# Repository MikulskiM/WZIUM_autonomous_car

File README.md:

# WZIUM_autonomous_car - ROS section
Autonomous RC car project

Clone repo and place it in 'wzium' directory. Please place this repo in user's home directory as some environmental variables depend on it later.
```
git clone https://github.com/MikulskiM/WZIUM_autonomous_car.git wzium
```

## Requirements
TODO: place link to raspberry pi image 

### ROS Melodic
Available only on Ubuntu 18.04 LTS.
Link to install [here](http://wiki.ros.org/melodic/Installation/Ubuntu).

Some setup in ~/.bashrc file:
```
# Networking - substitute <ip_address> with raspberry ip address
export ROS_MASTER_URI=http://<ip_address>:11311
export ROS_IP=<ip_address>

# Add to ros packages - can cause warning before first compile
export ROS_PACKAGE_PATH=~/wzium:${ROS_PACKAGE_PATH}
export CMAKE_PREFIX_PATH=~/wzium/devel:${CMAKE_PREFIX_PATH}

# Makes your package visible to ros at creating new console
source ~/wzium/devel/setup.bash
```

After setup you should bashrc so the changes can take place
```
source ~/.bashrc
```

To install ROS packages dependencies (run from workspace root directory):
```
rosdep install --from-paths src --ignore-src -r -y
```

## Build
Enter workspace root directory ('wzium')
```
catkin_make
source devel/setup.bash
```

Building packages can get lousy. You can add flag --pkg to catkin_make to specify packages that are to be built, e.g. ```catkin_make --pkg wzium```. This can save a lot of time.

## Usage
You can run nodes directly (you have to run ```roscore``` first in some console window), then run node e.g.:
```
# cpp nodes have to be built
rosrun wzium example_cpp_node
# python nodes have to be made executable
rosrun wzium example_python_node
```
or via launch files (no roscore needed) e.g.:
```
roslaunch wzium example_launch.launch
```

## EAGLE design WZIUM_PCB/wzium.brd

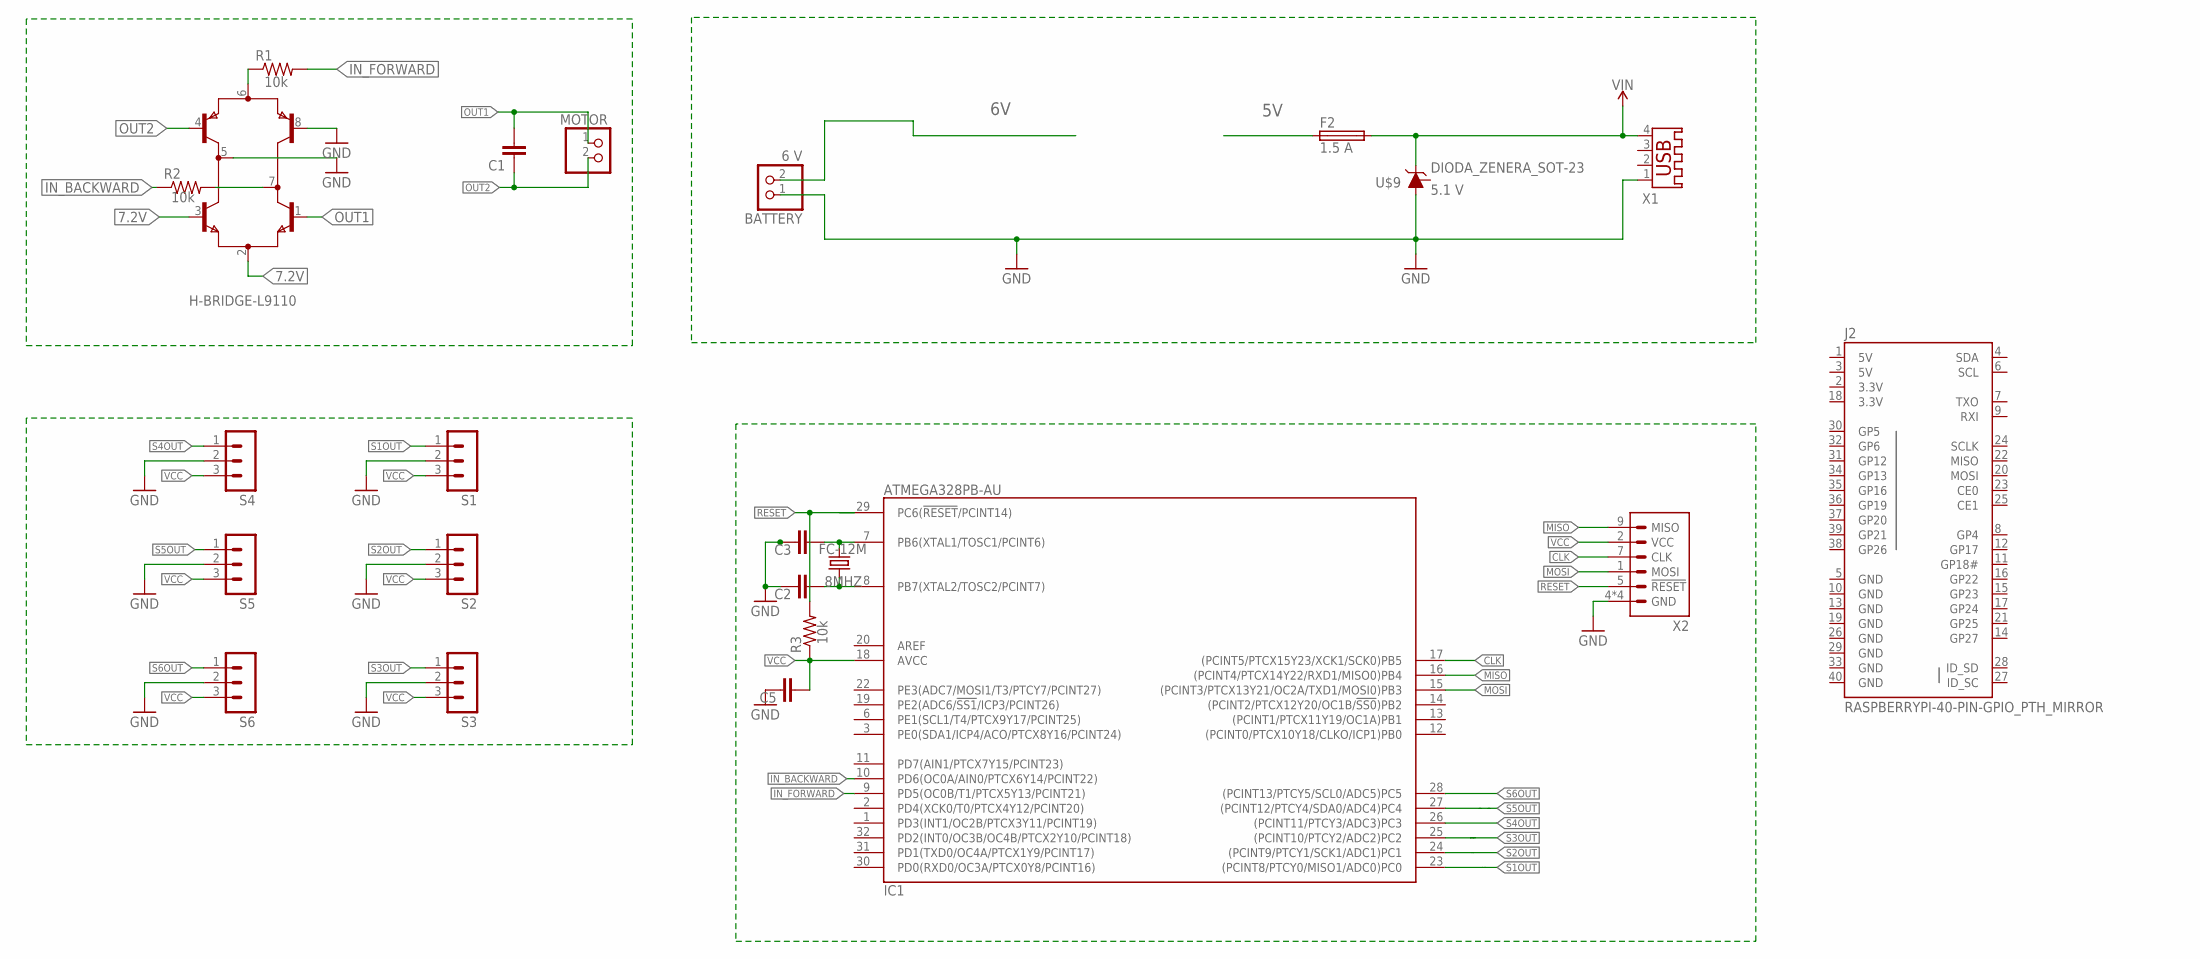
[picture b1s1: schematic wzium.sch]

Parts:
8MHZ: FC-12M
BATTERY: 6 V; 1X02
C1, C2, C3, C5: C-EUC0805; C0805
F2: 1.5 A; SH22,5
H-BRIDGE-L9110: H-BRIDGE; SM8
IC1: ATMEGA328PB-AU; QFP32_7X7_0.80
J2: RASPBERRYPI-40-PIN-GPIO_PTH_MIRROR; 2X20_SHROUDED
MOTOR: PINHD-1X2; 1X02
R1, R2, R3: 10k; R0805
S1, S2, S3, S4, S5, S6: MA03-1
U$9: DIODA_ZENERA_SOT-23; SOT23-3
X1: USB-A003
X2: MISO_MOSIIDC-10V; IDC-10V

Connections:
3.3V: J2.2 (3.3V), J2.18 (3.3V)
5V: F2.1, J2.1 (5V), J2.3 (5V)
6V: BATTERY.2
7.2V: H-BRIDGE-L9110.2 (E2E3), H-BRIDGE-L9110.3 (B2)
CLK: IC1.17 ((PCINT5/PTCX15Y23/XCK1/SCK0)PB5), X2.7 (CLK)
GND: BATTERY.1, C2.2, C3.2, C5.2, H-BRIDGE-L9110.5 (C1C2), H-BRIDGE-L9110.8 (B4), IC1.5 (GND), IC1.21 (GND), J2.5 (GND), J2.10 (GND), J2.13 (GND), J2.19 (GND), J2.26 (GND), J2.29 (GND), J2.33 (GND), J2.40 (GND), S1.2, S2.2, S3.2, S4.2, S5.2, S6.2, U$9.1 (A), X1.1, X2.4 (GND), X2.6 (GND), X2.8 (GND), X2.10 (GND)
IN_BACKWARD: IC1.10 (PD6(OC0A/AIN0/PTCX6Y14/PCINT22)), R2.1
IN_FORWARD: IC1.9 (PD5(OC0B/T1/PTCX5Y13/PCINT21)), R1.2
MISO: IC1.16 ((PCINT4/PTCX14Y22/RXD1/MISO0)PB4), X2.9 (MISO)
MOSI: IC1.15 ((PCINT3/PTCX13Y21/OC2A/TXD1/MOSI0)PB3), X2.1 (MOSI)
unnamed: H-BRIDGE-L9110.7 (C3C4), R2.2
unnamed: H-BRIDGE-L9110.6 (E1E4), R1.1
unnamed: 8MHZ.1, C3.1, IC1.7 (PB6(XTAL1/TOSC1/PCINT6))
unnamed: 8MHZ.2, C2.1, IC1.8 (PB7(XTAL2/TOSC2/PCINT7))
OUT1: C1.2, H-BRIDGE-L9110.1 (B3), MOTOR.1
OUT2: C1.1, H-BRIDGE-L9110.4 (B1), MOTOR.2
RESET: IC1.29 (PC6(!RESET!/PCINT14)), R3.2, X2.5 (!RESET)
S1OUT: IC1.23 ((PCINT8/PTCY0/MISO1/ADC0)PC0), S1.1
S2OUT: IC1.24 ((PCINT9/PTCY1/SCK1/ADC1)PC1), S2.1
S3OUT: IC1.25 ((PCINT10/PTCY2/ADC2)PC2), S3.1
S4OUT: IC1.26 ((PCINT11/PTCY3/ADC3)PC3), S4.1
S5OUT: IC1.27 ((PCINT12/PTCY4/SDA0/ADC4)PC4), S5.1
S6OUT: IC1.28 ((PCINT13/PTCY5/SCL0/ADC5)PC5), S6.1
VCC: C5.1, IC1.4 (VCC), IC1.18 (AVCC), R3.1, S1.3, S2.3, S3.3, S4.3, S5.3, S6.3, X2.2 (VCC)
VIN: F2.2, U$9.3 (C), X1.4

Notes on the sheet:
5.1 V

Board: 2 copper layers, 27 parts (0 on the bottom side), 24 nets, no tracks yet.

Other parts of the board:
U$1, U$3, U$4, U$5: M3-HOLE

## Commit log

2021-03-23 [ADD][PCB] Początek projektu EAGLE
    + projekt EAGLE
    + otwory montażowe w dobrych miejscach
    + gniazdo na taśmę z RPi w dobrą stronę
2021-03-23 [ADD][3D PRINT] Dodałem prosty uchwyt na kamerkę dla Maćka
    + prosty uchwyt na kamerkę dla Maćka z mojej inżynierki, żeby łatwiej było mu zacząć (SPRAWDŹ WYMIARY Z RZECZYWISTĄ KAMERKĄ / DOKUMENTACJĄ KAMERKI)
2021-03-23 [ADD][PCB] Dodano schemat zasilania RPi i poprawiono wymiary
2021-03-25 [PCB] Zmieniono wielkość płytki na 10x10
    Docelowo myślimy o JLC PCB, więc przeanalizowałem ich ceny:
    -> 2.2 $ za płytkę 10x10 cm
    -> 8.8 $ za płytkę 10x12 cm
    Spróbujmy zmieścić się na płytce 10x10. Jeśli to niemożliwe to zmienimy rozmiar. Duże moduły można zamontować na podwoziu obok płytki ze sterownikiem i połączyć kablami.
2021-03-28 change license to WTFPL
2021-03-28 init ros package
2021-03-28 [PCB] Upgraded to EAGLE 9.6.2 i dodano biblioteki
2021-03-28 add raspicam node
2021-03-28 update readme about dependencies
2021-03-28 initialise roadsign detector node
2021-03-30 [ADD][3D PRINT] Dodałem pierwszy, wstępny projekt platformy
    - kształt samej powierzchni podstawki jak i mocowań do nadwozia może ulegać zmianom,
    - rozstaw podpórek powinien być zgodny z rozstawem uchwytów na podwoziu,
    - obecny model podstawki jest do zamontowania bez karoserii - w kolejnych wersjach będzie to wymagało poprawki,
    - konieczne będzie jeszcze dodanie otworów montażowych na dystanse do płytki PCB
2021-04-05 [FIX][ADD][PCB] Naprawiłem kolejnośc pinów od RPi na PCB | dodałem obrys RPi,
    piny od RPi na 100% będą właśnie w tej konfiguracji. Obrazek na płytce póki co może być mylący, bo gniazdo FC 40p powinno mieć "ząbek" po drugiej stronie, ale postaram się to naprawić później. Dodałe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
2021-04-08 [FIX][PCB] Poprawiłem obrys gniazda FC 40p
    Potwierdzam też kolejność pinów w tym gnieździe, zgadza się i jest ok
2021-04-10 dodanie sekcji sterowania silnikiem i AVR, dodanie .gitignore
2021-04-11 create roadsign_detector_package
2021-04-11 add movie launcherm ad video2bag script
2021-04-11 [ADD][3D PRINT] Dodałem przerobiony uchwyt na kamerkę
    TODO:
    - dodać staw przy mocowaniu kamerki
    - rozważyć zmianę koncepcji odnośnie samej odnogi pomiędzy podstawą, a mocowaniem
2021-04-12 fix color encoding, add dependency and readme
2021-04-16 add red and blue mask
2021-04-17 dodano sekcje czujnikow odleglosci Sharp GP2Y0A41SK0F
2021-04-18 [3D PRINT] podstawka - zmiana kształtu
    - dodano otwory montażowe oraz dołki na nakrętki do śrub M3,
    - kształt podstawki przypomina kształtem nadwozie samochodu,
    - rozstaw podpórek pozostał bez zmian,
    - w tej wersji powinna być możliwość zamocowania karoserii po wstawieniu podstawki.
2021-04-22 add red signs detection
2021-04-22 add blue algorithm
2021-04-22 update rviz config
2021-04-22 add rs_detector launch file
2021-05-18 Add neural network files
2021-05-26 [3D PRINT] podstawka - zmniejszenie rozmiaru
    - zmniejszono wielkość podstawki,
    - przygotowano otwory na zamocowanie dystansów oraz nakrętek do śrub.
2021-05-26 [3D PRINT] podstawka - wydłużenie dystansów
    - wydłużono dystanse na których ma opierać się podstawka, zapewniając 5mm odstępu od nadwozia.
2021-06-01 [3D PRINT] podstawka - zmniejszenie powierzchni płaskiej
    - usunięto puste pole na środku podstawki,
    - ścięto narożniki,
    - wyrównano krawędzie boczne.

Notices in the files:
parts and their libraries:
SparkFun-DiscreteSemi: Licensing: Creative Commons ShareAlike 4.0 International - https://creativecommons.org/licenses/by-sa/4.0
